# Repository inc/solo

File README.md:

# SOLO IOT motor controller

## Overview

SOLO is an IOT motor controller board designed by Lone Dynamics.

## Features

  * Supports ESPEasy to provide a web-based interface and MQTT support over WiFi
  * Controls 2 (bidirectional) or 4 (unidirectional) DC motors
  * Power via MicroUSB or batteries and a solar panel
  * Battery voltage monitoring
  * Hand-solderable with a soldering iron

## Specifications

| | |
| --- | --- |
| Dimensions | 65mm x 60mm |
| WiFi Module | ESP-12E or F |
| Motor Controller | L293D |
| Power | MicroUSB, 4xAA NiMH batteries, 6V solar panel |

## Header Pinout

| Pin | Function |
| --- | --- |
| 1 | VCCBAT |
| 2 | VCC3V3 |
| 3 | ESPTXD |
| 4 | ESPRXD |
| 5 | ESPRST |
| 6 | GND |
| 7 | MOTOR12EN |
| 8 | MOTOR34EN |
| 9 | MOTOR1A |
| 10 | MOTOR2A |
| 11 | MOTOR3A |
| 12 | MOTOR4A |

## Board

## Schematics

## Known Issues (revision 0)

  * Pull-down resistors (10K) should be added to MOTOR12EN and MOTOR34EN to prevent the L293D from being enabled while the ESP is in sleep mode
  * Heatsink cutout doesn't expose copper
  * Has no built-in battery over-voltage protection

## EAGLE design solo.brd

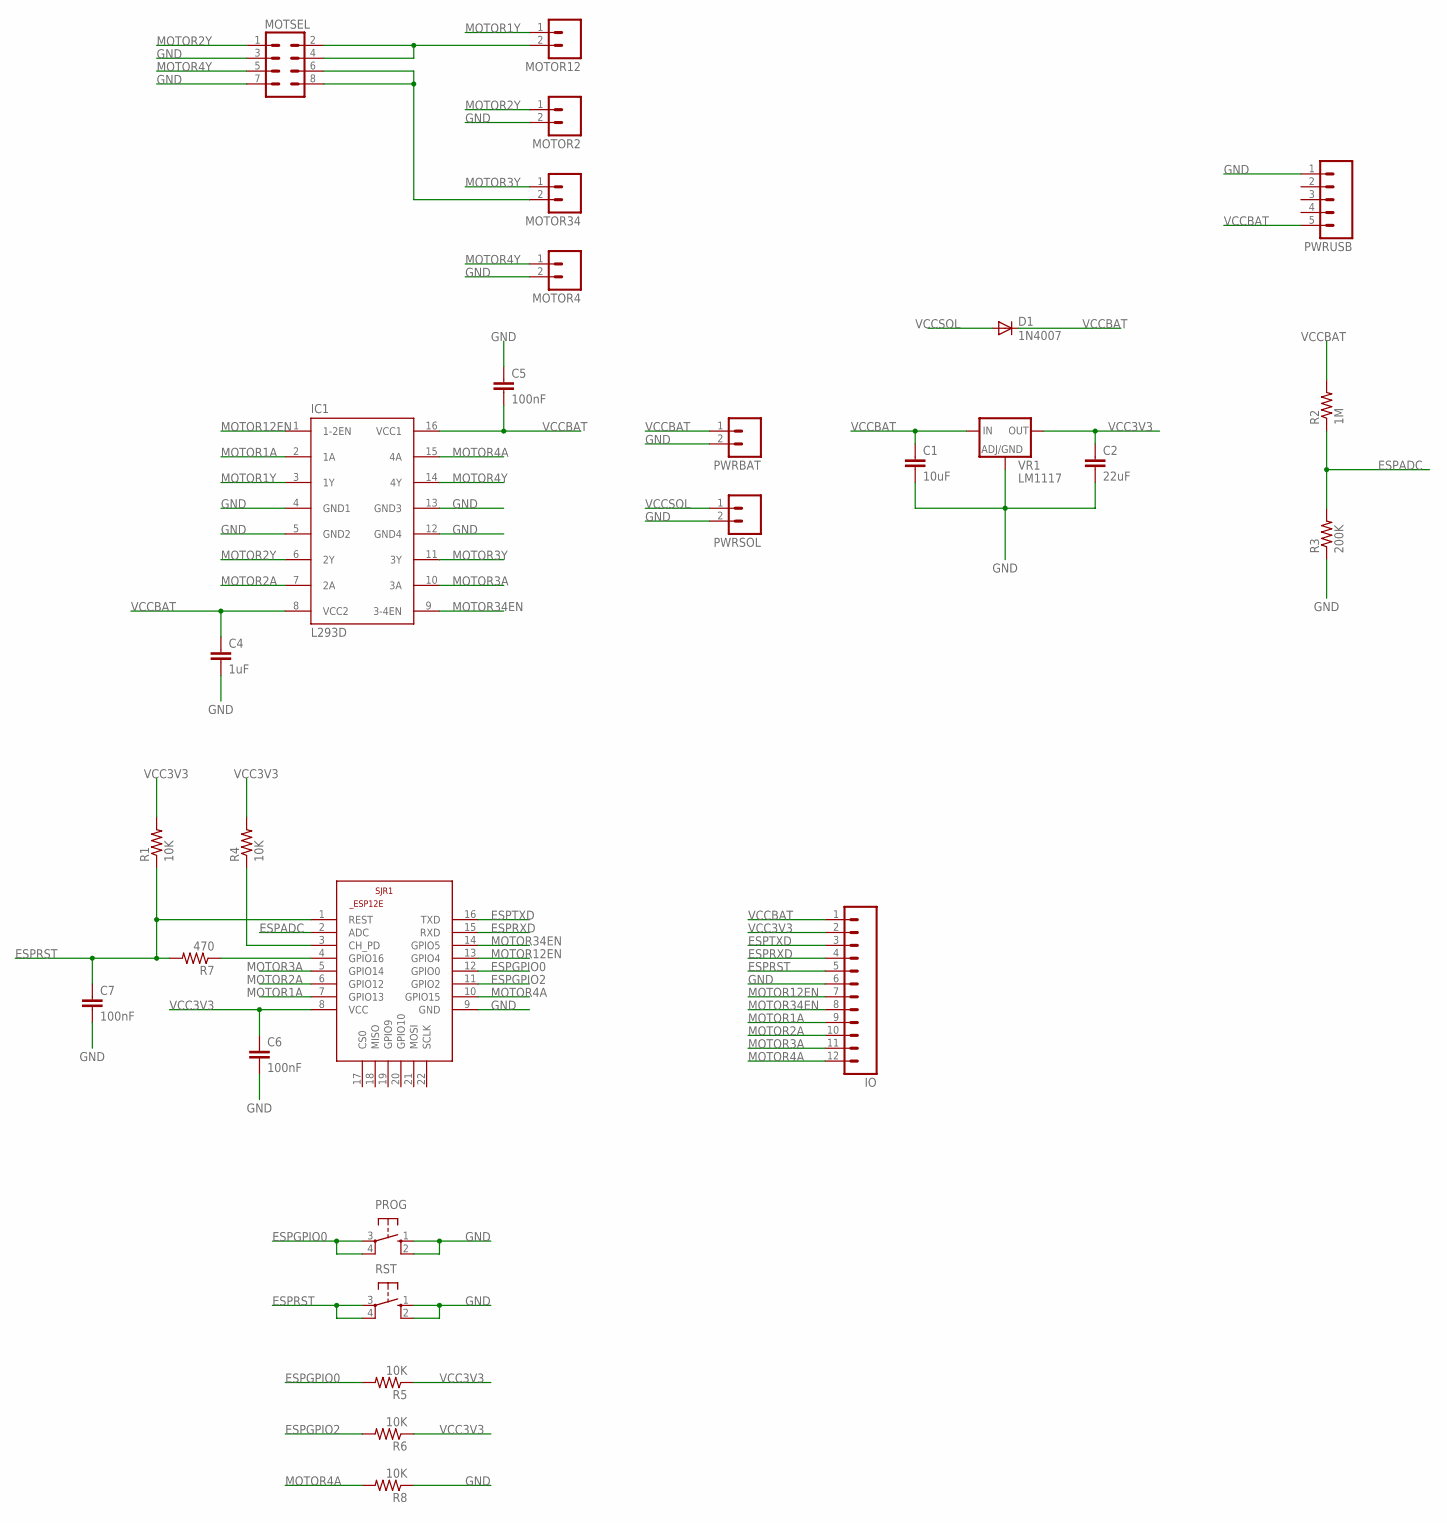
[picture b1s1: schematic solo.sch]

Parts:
C1: 10uF; 1206
C2: 22uF; 1206
C4: 1uF; 1206
C5, C6, C7: 100nF; 1206
D1: 1N4007; DO41-10
IC1: L293D; DIL16
IO: M12PTH; 1X12
MOTOR2, MOTOR4, MOTOR12, MOTOR34: M023.5MM; SCREWTERMINAL-3.5MM-2
MOTSEL: M04X2; 2X4
PROG: 10-XX; B3F-10XX
PWRBAT: M023.5MM; SCREWTERMINAL-3.5MM-2
PWRSOL: M023.5MM; SCREWTERMINAL-3.5MM-2
PWRUSB: M05PTH; 1X05
R1, R4, R5, R6, R8: 10K; 1206
R2: 1M; 1206
R3: 200K; 1206
R7: 470; 1206
RST: 10-XX; B3F-10XX
SJR1: ESP8266-12EESP12E; ESP8266-ESP12E
VR1: LM1117; SOT223

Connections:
ESPADC: R2.1, R3.2, SJR1.2 (ADC)
ESPCHPD: R4.1, SJR1.3 (CH_PD)
ESPGPIO0: PROG.3, PROG.4 (P1), R5.2, SJR1.12 (GPIO0)
ESPGPIO2: R6.2, SJR1.11 (GPIO2)
ESPRST: C7.1, IO.5, R1.1, R7.2, RST.3, RST.4 (P1), SJR1.1 (REST)
ESPRXD: IO.4, SJR1.15 (RXD)
ESPTXD: IO.3, SJR1.16 (TXD)
GND: C1.2, C2.2, C4.2, C5.1, C6.2, C7.2, IC1.4 (GND1), IC1.5 (GND2), IC1.12 (GND4), IC1.13 (GND3), IO.6, MOTOR2.2, MOTOR4.2, MOTSEL.3, MOTSEL.7, PROG.1 (S), PROG.2 (S1), PWRBAT.2, PWRSOL.2, PWRUSB.1, R3.1, R8.1, RST.1 (S), RST.2 (S1), SJR1.9 (GND), VR1.1 (ADJ/GND)
MOTOR1A: IC1.2 (1A), IO.9, SJR1.7 (GPIO13)
MOTOR1Y: IC1.3 (1Y), MOTOR12.1
MOTOR2A: IC1.7 (2A), IO.10, SJR1.6 (GPIO12)
MOTOR2Y: IC1.6 (2Y), MOTOR2.1, MOTSEL.1
MOTOR3A: IC1.10 (3A), IO.11, SJR1.5 (GPIO14)
MOTOR3Y: IC1.11 (3Y), MOTOR34.1
MOTOR4A: IC1.15 (4A), IO.12, R8.2, SJR1.10 (GPIO15)
MOTOR4Y: IC1.14 (4Y), MOTOR4.1, MOTSEL.5
MOTOR12EN: IC1.1 (1-2EN), IO.7, SJR1.13 (GPIO4)
MOTOR34EN: IC1.9 (3-4EN), IO.8, SJR1.14 (GPIO5)
unnamed: MOTOR12.2, MOTSEL.2, MOTSEL.4
unnamed: MOTOR34.2, MOTSEL.6, MOTSEL.8
unnamed: R7.1, SJR1.4 (GPIO16)
VCC3V3: C2.1, C6.1, IO.2, R1.2, R4.2, R5.1, R6.1, SJR1.8 (VCC), VR1.2 (OUT)
VCCBAT: C1.1, C4.1, C5.2, D1.C, IC1.8 (VCC2), IC1.16 (VCC1), IO.1, PWRBAT.1, PWRUSB.5, R2.2, VR1.3 (IN)
VCCSOL: D1.A, PWRSOL.1

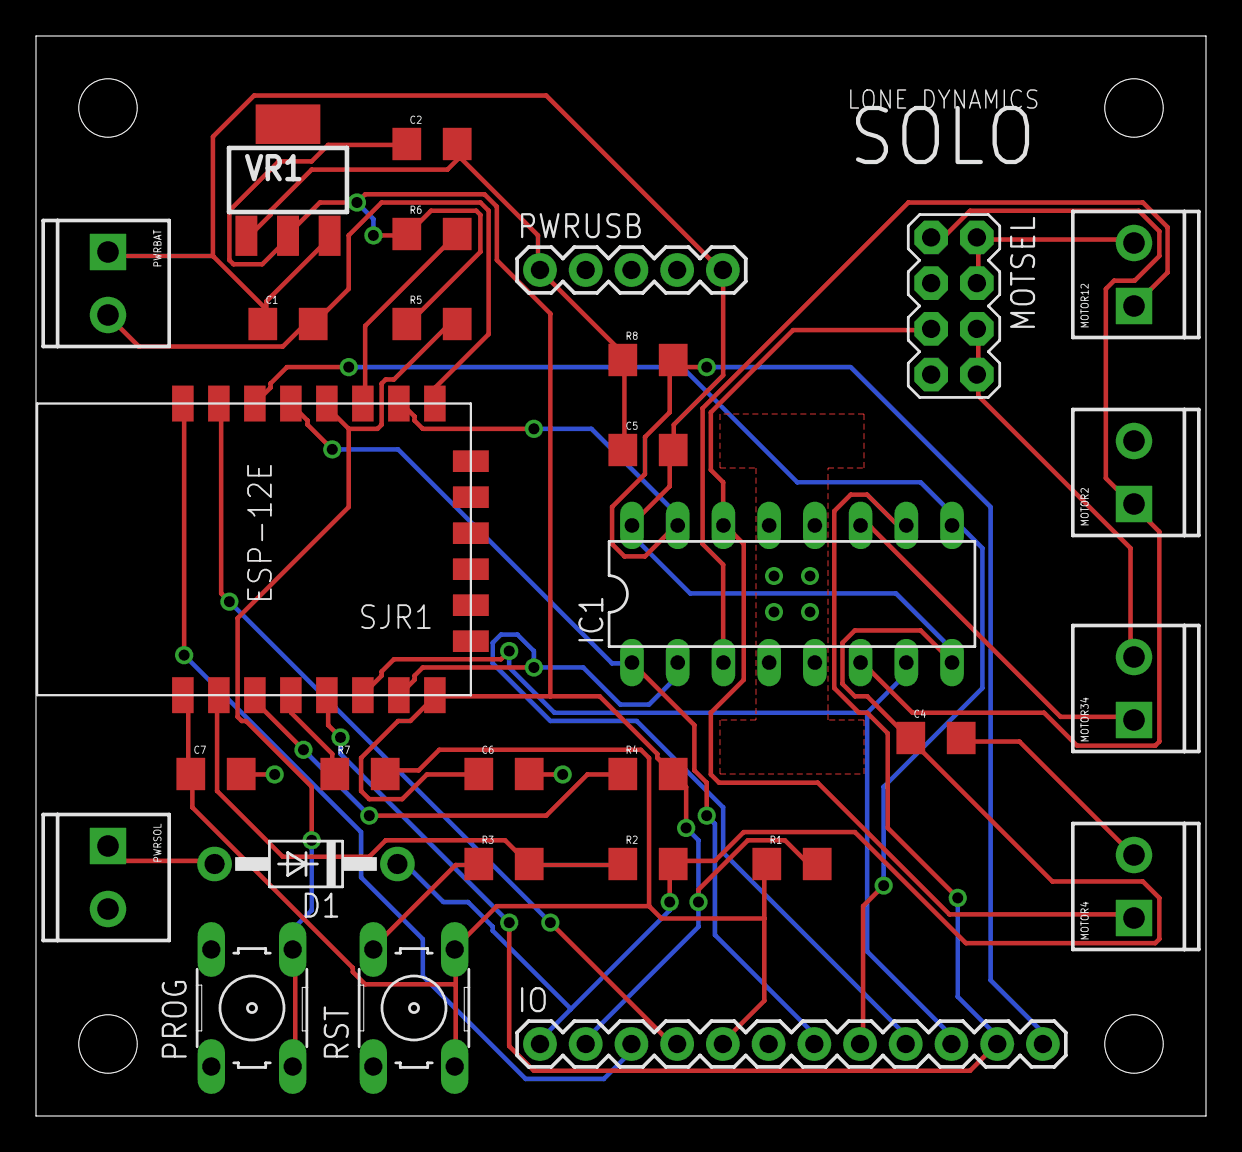
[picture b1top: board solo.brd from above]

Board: 2 copper layers, 65.0 x 60.0 mm, 29 parts (0 on the bottom side), 24 nets.

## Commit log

2020-04-01 add license

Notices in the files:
parts and their libraries:
SparkFun-Connectors: Licensing: Creative Commons ShareAlike 4.0 International - https://creativecommons.org/licenses/by-sa/4.0
